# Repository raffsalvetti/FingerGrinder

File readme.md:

# FingerGrinder Gamepad

FingerGrinder is a gamepad project build using the Atmel ATtiny85 microcontroller, shift registers, some passive components and firmware based on the V-USB library.  
Find details about this build here: https://raffsalvetti.dev/2023/07/attiny85-gamepad/
You can find more about the V-USB library at: https://www.obdev.at/vusb/

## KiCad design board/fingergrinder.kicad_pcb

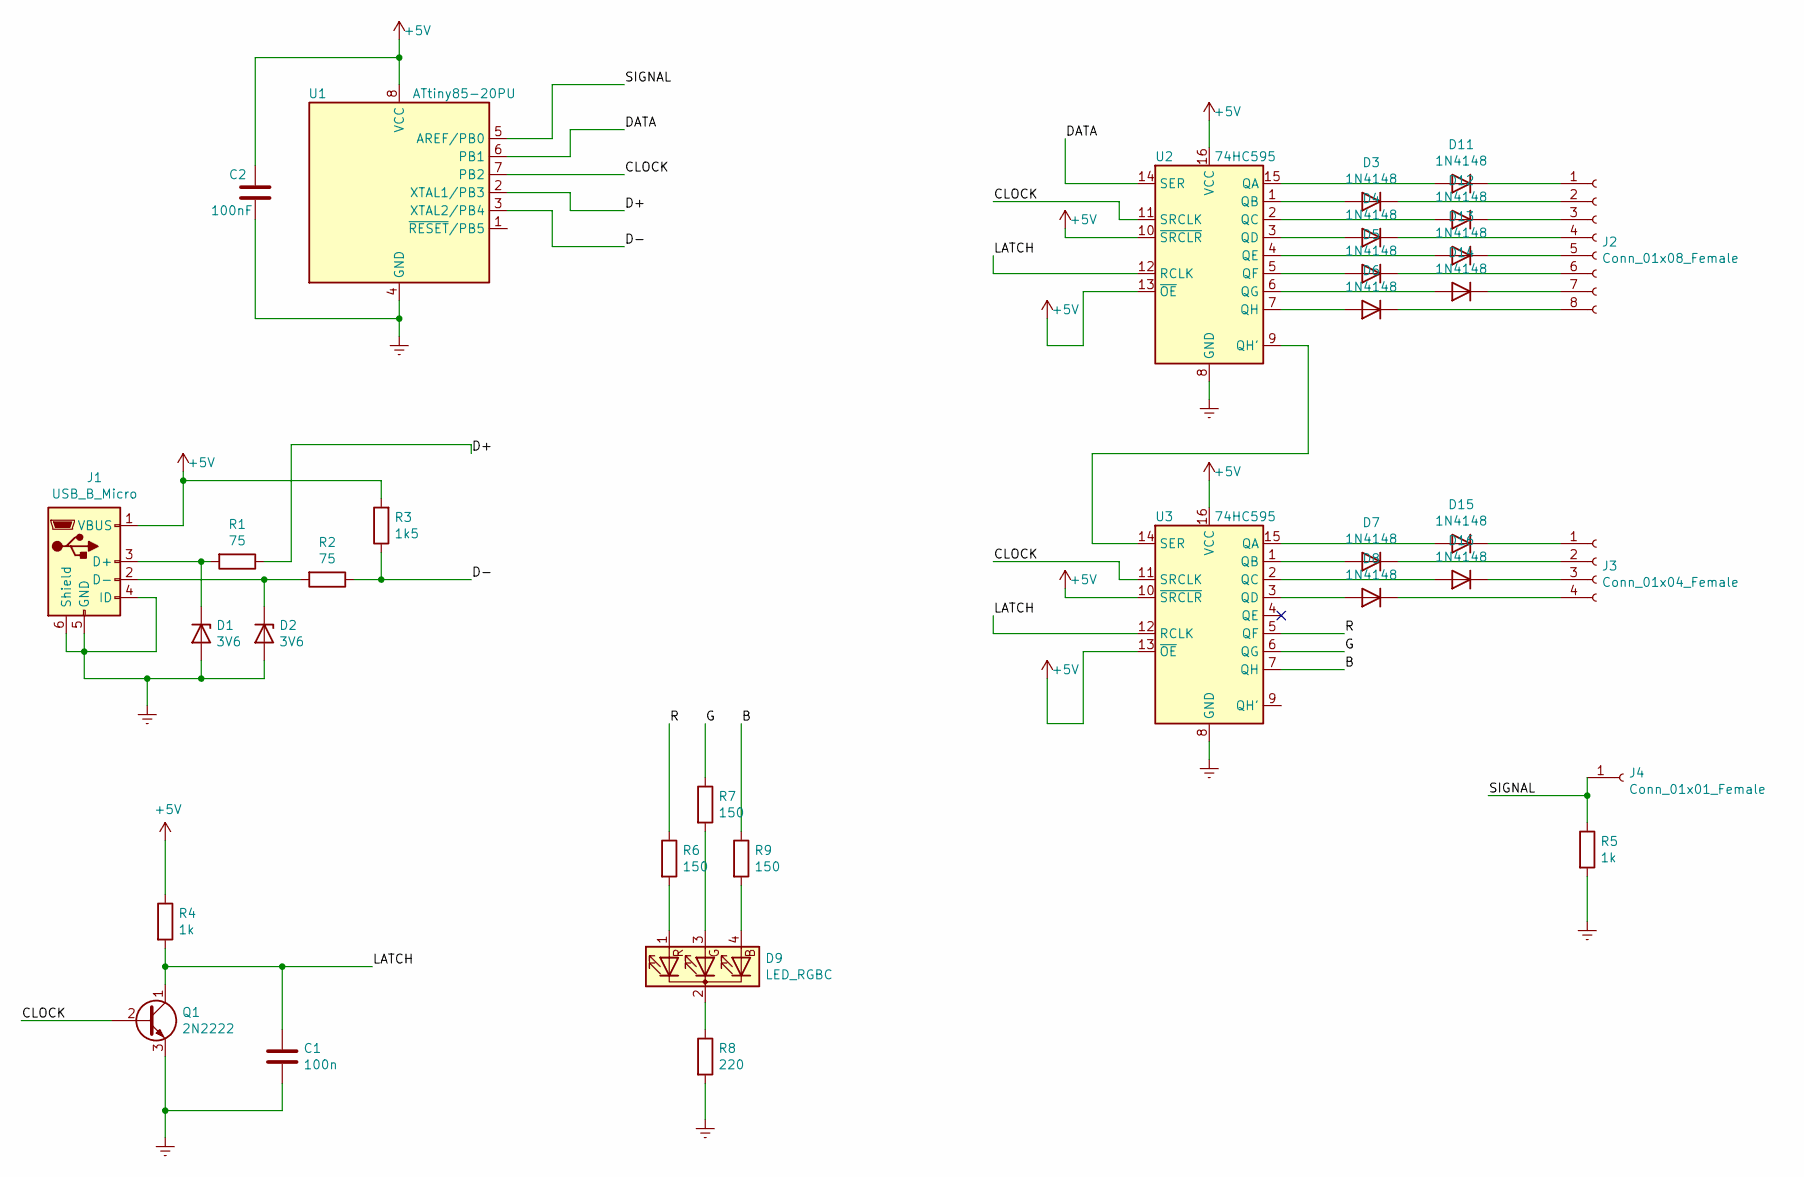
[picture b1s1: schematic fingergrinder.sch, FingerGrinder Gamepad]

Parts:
C1: 100n; C_Disc_D4.7mm_W2.5mm_P5.00mm
C2: 100nF; C_Disc_D4.7mm_W2.5mm_P5.00mm
D1, D2: 3V6; D_DO-35_SOD27_P2.54mm_Vertical_AnodeUp
D3, D4, D5, D6, D7, D8, D11, D12, D13, D14, D15, D16: 1N4148; D_DO-35_SOD27_P7.62mm_Horizontal
D9: LED_RGBC; LED_D5.0mm-4_RGB_Wide_Pins
J1: USB_B_Micro; PinHeader_1x06_P2.54mm_Vertical
J2: Conn_01x08_Female; PinHeader_1x08_P2.54mm_Vertical
J3: Conn_01x04_Female; PinHeader_1x04_P2.54mm_Vertical
J4: Conn_01x01_Female; PinHeader_1x01_P2.54mm_Vertical
Q1: 2N2222; TO-92_Inline_Wide
R1, R2: 75; R_Axial_DIN0207_L6.3mm_D2.5mm_P2.54mm_Vertical
R3: 1k5; R_Axial_DIN0207_L6.3mm_D2.5mm_P2.54mm_Vertical
R4, R5: 1k; R_Axial_DIN0207_L6.3mm_D2.5mm_P2.54mm_Vertical
R6, R7, R9: 150; R_Axial_DIN0207_L6.3mm_D2.5mm_P2.54mm_Vertical
R8: 220; R_Axial_DIN0207_L6.3mm_D2.5mm_P2.54mm_Vertical
U1: ATtiny85-20PU; DIP-8_W7.62mm
U2, U3: 74HC595; DIP-16_W7.62mm

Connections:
+5V: C2.1, J1.1 (VBUS), R3.2, R4.1, U1.8 (VCC), U2.10 (~SRCLR), U2.13 (~OE), U2.16 (VCC), U3.10 (~SRCLR), U3.13 (~OE), U3.16 (VCC)
/B: R9.1, U3.7 (QH)
/CLOCK: Q1.2 (B), U1.7 (PB2), U2.11 (SRCLK), U3.11 (SRCLK)
/D+: R1.1, U1.2 (XTAL1/PB3)
/D-: R2.1, R3.1, U1.3 (XTAL2/PB4)
/DATA: U1.6 (PB1), U2.14 (SER)
/G: R7.1, U3.6 (QG)
/LATCH: C1.1, Q1.1 (C), R4.2, U2.12 (RCLK), U3.12 (RCLK)
/R: R6.1, U3.5 (QF)
/SIGNAL: J4.1, R5.1, U1.5 (AREF/PB0)
Earth: C1.2, C2.2, D1.2 (A), D2.2 (A), J1.4 (ID), J1.5 (GND), J1.6 (Shield), Q1.3 (E), R5.2, R8.2, U1.4 (GND), U2.8 (GND), U3.8 (GND)
unnamed: D1.1 (K), J1.3 (D+), R1.2
unnamed: D2.1 (K), J1.2 (D-), R2.2
unnamed: D3.1 (K), J2.2
unnamed: D3.2 (A), U2.1 (QB)
unnamed: D4.1 (K), J2.4
unnamed: D4.2 (A), U2.3 (QD)
unnamed: D5.1 (K), J2.6
unnamed: D5.2 (A), U2.5 (QF)
unnamed: D6.1 (K), J2.8
unnamed: D6.2 (A), U2.7 (QH)
unnamed: D7.1 (K), J3.2
unnamed: D7.2 (A), U3.1 (QB)
unnamed: D8.1 (K), J3.4
unnamed: D8.2 (A), U3.3 (QD)
unnamed: D9.1 (RA), R6.2
unnamed: D9.2 (K), R8.1
unnamed: D9.3 (GA), R7.2
unnamed: D9.4 (BA), R9.2
unnamed: D11.1 (K), J2.1
unnamed: D11.2 (A), U2.15 (QA)
unnamed: D12.1 (K), J2.3
unnamed: D12.2 (A), U2.2 (QC)
unnamed: D13.1 (K), J2.5
unnamed: D13.2 (A), U2.4 (QE)
unnamed: D14.1 (K), J2.7
unnamed: D14.2 (A), U2.6 (QG)
unnamed: D15.1 (K), J3.1
unnamed: D15.2 (A), U3.15 (QA)
unnamed: D16.1 (K), J3.3
unnamed: D16.2 (A), U3.2 (QC)
unnamed: U2.9 (QH'), U3.14 (SER)

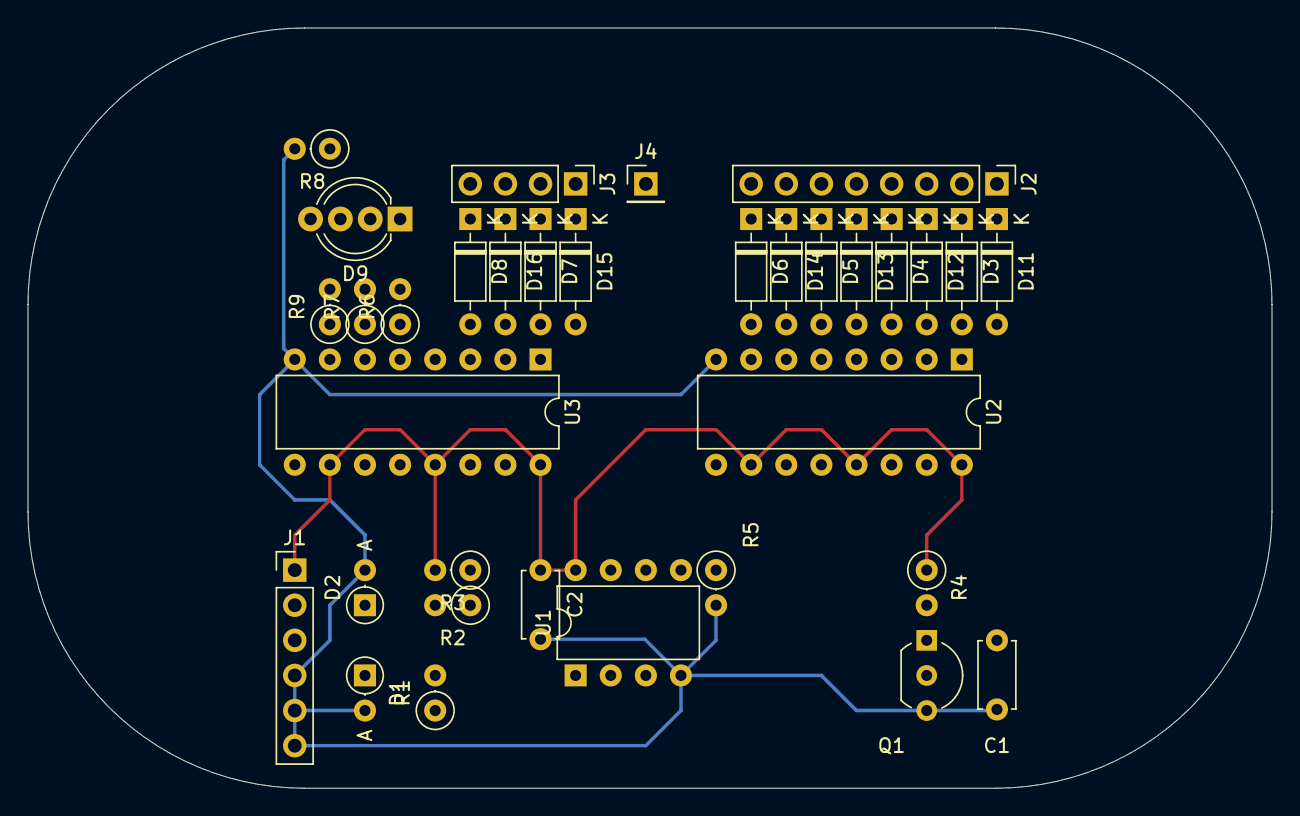
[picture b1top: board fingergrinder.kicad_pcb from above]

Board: 2 copper layers, 90.0 x 55.0 mm, 34 parts (0 on the bottom side), 42 nets.

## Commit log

2023-08-09 share
